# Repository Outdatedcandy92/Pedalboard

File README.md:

# DIY Guitar Pedals

>This project aims to create a DIY friendly and Mod-able version of  the iconic Boss DS-1 and Big Muff Pi.

Modern guitar pedals such as the DS-1 and Big Muff Pi are **super expensive**!! and the new pedals that are being produced all have SMD components which make it harder to mod and repair. I always wanted to get a DS-1 but its price tag really put me off, so I did a bit of research and found a really good circuit analysis of the DS-1 on [ElectroSmash's Website](https://www.electrosmash.com/boss-ds1-analysis) and decided to create my own [DS-1](https://github.com/Outdatedcandy92/DistortionPedal) and it was really rewarding project and the results were also very good. 
Since my DS-1 Version 1 had really good results, I decided to design an even upgraded version of it which fixes problems in version 1, In addition to that I also created a PCB for the Big Muff Pi.

https://github.com/user-attachments/assets/e87293e5-299d-45d1-807d-6a7f5c813e14

https://github.com/user-attachments/assets/bea94fd8-728a-4ede-ab68-e8244417e8f7

*DS-1 PCB*

*Big Muff PCB*

---

### DS-1

### Big Muff Pi

### 3PDT Breakout Board (Optional)

  ---
## BOM

More detailed BOM with parts lists is under the `src` folder 

### DS-1 Components
| **Reference**              | **Value / Part Number**           |
| -------------------------- | --------------------------------- |
| C1, C3                     | 47n                               |
| C2, C8, C9                 | 0.47µF                            |
| C4                         | 250pF                             |
| C5                         | 68n                               |
| C7                         | 100pF                             |
| C10                        | 0.01µF                            |
| C11                        | 0.022µF                           |
| C12                        | 0.1µF                             |
| C13                        | 0.047µF                           |
| C14                        | 1µF                               |
| C15                        | 47µF                              |
| C23                        | 100µF                             |
| D1                         | 1N4004                            |
| D4, D5, D8                 | D1N4148                           |
| Q1, Q2, Q3                 | 2SC2240                           |
| R1, R22                    | 1K                                |
| R2, R7                     | 470K                              |
| R3, R8, R18, R21, R24, R25 | 10K                               |
| R4, R5, R10, R11, R23      | 100K                              |
| R9                         | 22Ω                               |
| R13                        | 4.7K                              |
| R14, R15                   | 2.2K                              |
| R16, R17                   | 6.8K                              |
| R19, R20                   | 1M                                |
| R39                        | 47K                               |
| U1                         | NJM3404A (M5223AL, BA728N equiv.) |
| VR1, VR2                   | 100KB                             |
| VR3                        | 20KB                              |
| J1, J2                     | 6.35mm Jacks                      |
|                            |                                   |

### Big Muff Pi

| **Component Type**       | **Value / Part Number**                           | **Designators**                     |
|--------------------------|---------------------------------------------------|-------------------------------------|
| NPN Transistors          | BC239 or 2N5088, 2N5089, BC549C, SE4010, 2N5210   | Q1, Q2, Q3, Q4                      |
| Silicon Diodes           | 1N914 or 1N4148                                   | D1, D2, D3, D4                      |
| Potentiometers (Lin)     | 100K                                              | Sustain, Tone, Volume              |
| Resistors                | 10K                                               | R13, R19, R18, R11, R12            |
| Resistors                | 100K                                              | R20, R16, R3                       |
| Resistors                | 470K                                              | R9, R17, R15                       |
| Resistors                | 39K                                               | R2, R8                             |
| Resistors                | 150                                               | R21, R10                           |
| Resistors                | 15K                                               | R6                                 |
| Resistor                 | 47K                                               | R14                                |
| Resistor                 | 100                                               | R22                                |
| Resistor                 | 3.3K                                              | R4                                 |
| Resistor                 | 1K                                                | R23                                |
| Resistor                 | 22K                                               | R5                                 |
| Capacitors               | 1µF                                               | C1, C4, C6, C7                     |
| Capacitors               | 100nF                                             | C5, C13, C3, C2                    |
| Capacitors               | 470pF                                             | C10, C11, C12                      |
| Capacitor                | 4nF                                               | C9                                 |
| Capacitor                | 10nF                                              | C8                                 |

#### Credits

[ElectroSmash Boss DS-1 Analysis](https://www.electrosmash.com/boss-ds1-analysis)
[ElectroSmash Big Muff Pi Analysis](https://www.electrosmash.com/big-muff-pi-analysis)

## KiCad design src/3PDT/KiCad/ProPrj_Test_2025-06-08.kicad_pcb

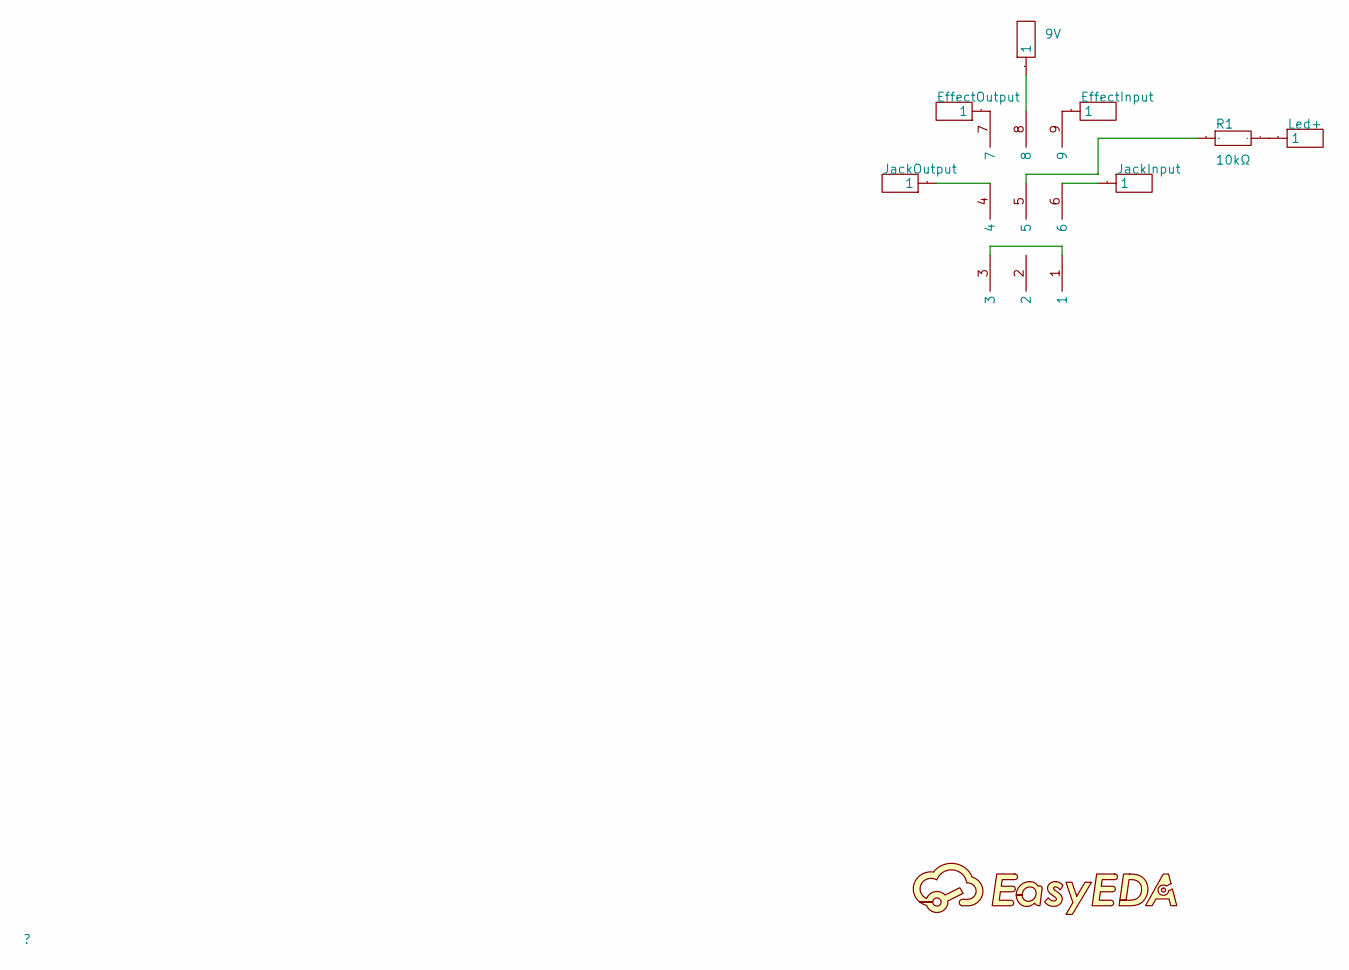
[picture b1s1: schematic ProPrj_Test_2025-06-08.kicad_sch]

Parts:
9V: HDR-TH_1P-V-M_XKB_X4611WV-01I-C28D40
EffectInput: HDR-TH_1P-V-M_XKB_X4611WV-01I-C28D40
EffectOutput: HDR-TH_1P-V-M_XKB_X4611WV-01I-C28D40
JackInput: HDR-TH_1P-V-M_XKB_X4611WV-01I-C28D40
JackOutput: HDR-TH_1P-V-M_XKB_X4611WV-01I-C28D40
Led+: HDR-TH_1P-V-M_XKB_X4611WV-01I-C28D40
R1: 10kΩ; R_AXIAL-0.4
U4: 3dpt

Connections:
$1N369: U4.1, U4.3
$1N418: JackOutput.1, U4.4
$1N421: JackInput.1, U4.6
$1N548: EffectInput.1, U4.9
$1N590: EffectOutput.1, U4.7
$1N612: 9V.1, U4.8
$1N706: Led+.1, R1.2
$1N710: R1.1, U4.5

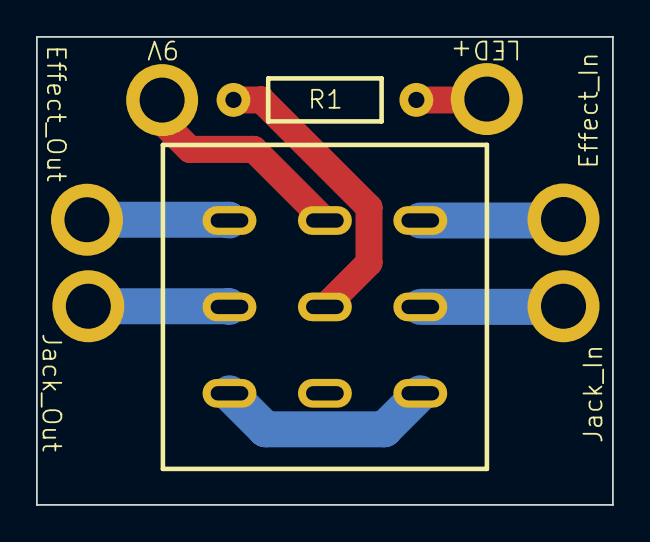
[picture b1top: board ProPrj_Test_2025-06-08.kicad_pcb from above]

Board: 2 copper layers, 32.0 x 26.0 mm, 8 parts (0 on the bottom side), 8 nets.

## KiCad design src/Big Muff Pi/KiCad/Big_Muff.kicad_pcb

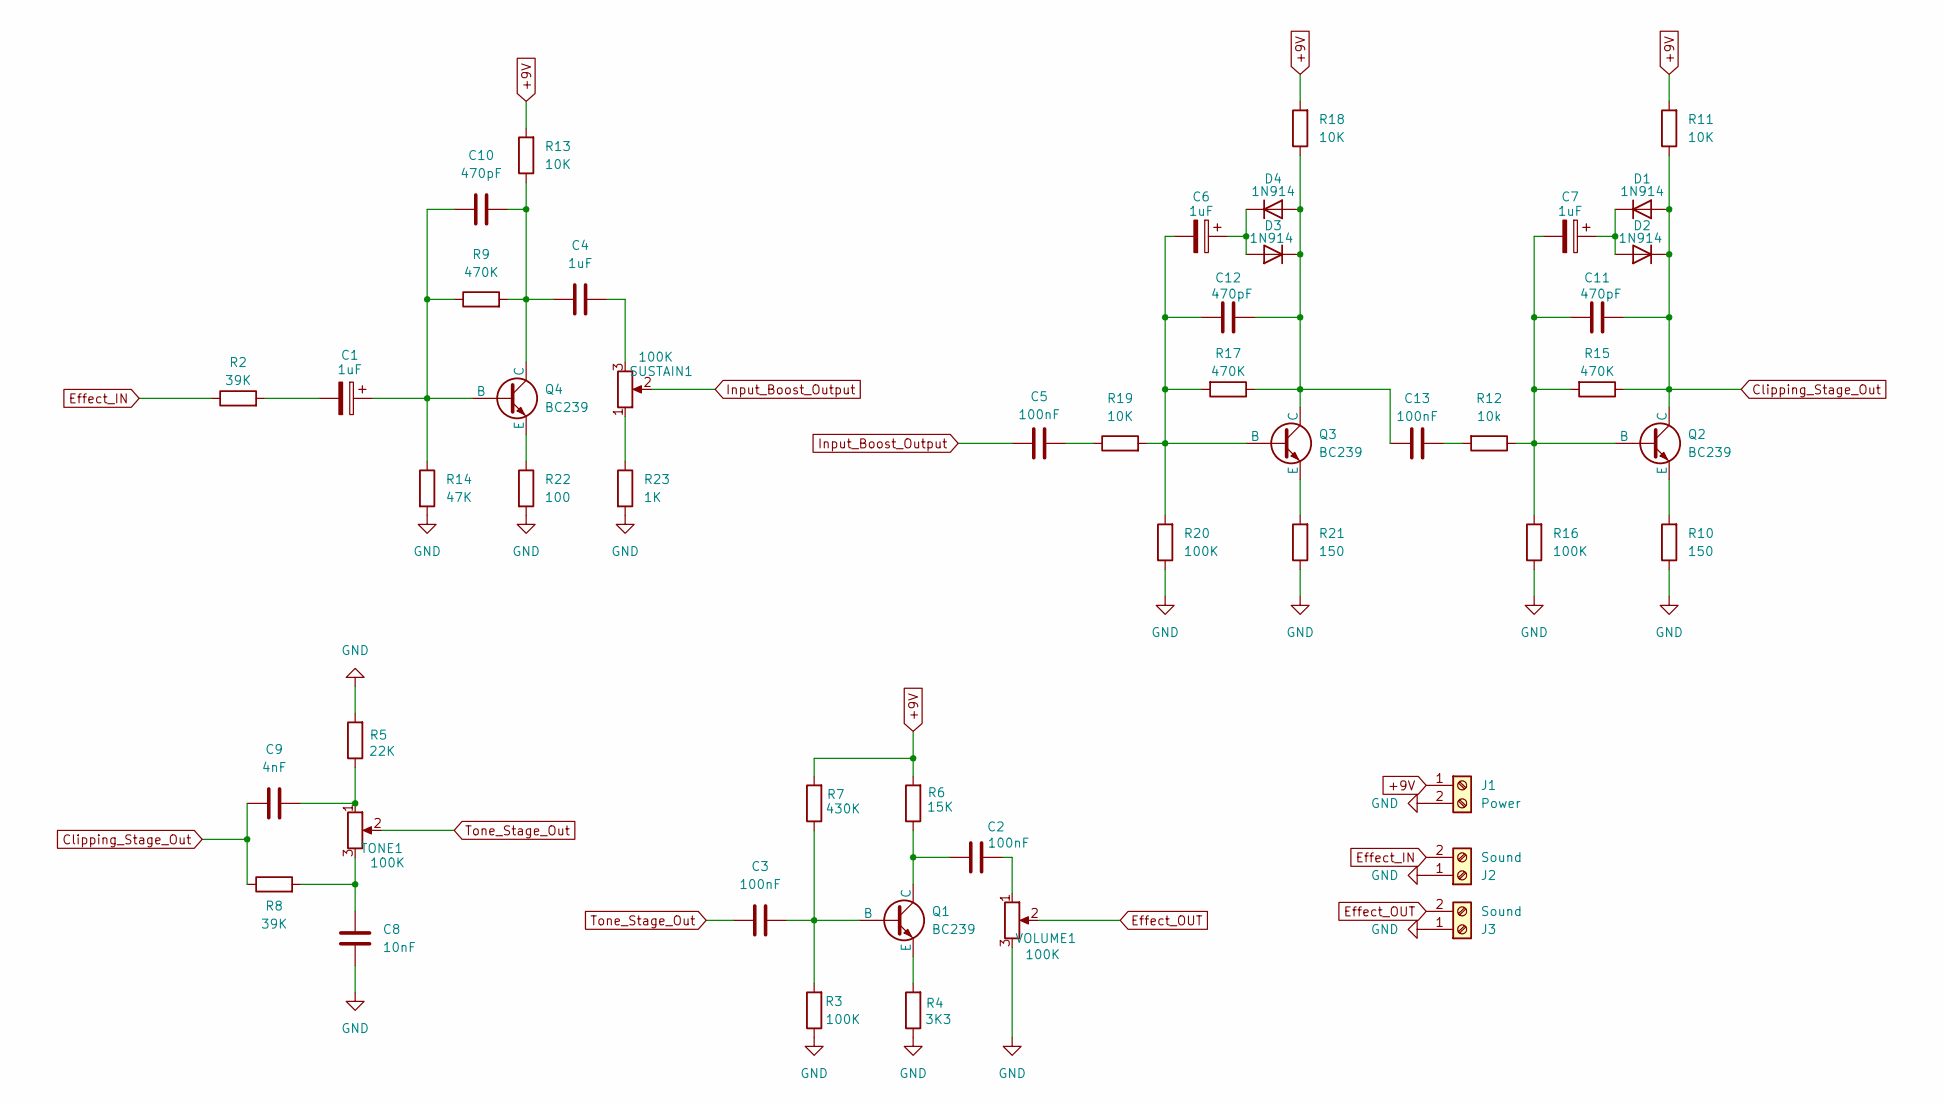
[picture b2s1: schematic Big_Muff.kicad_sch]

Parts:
C1, C6, C7: 1uF; CP_Radial_D5.0mm_P2.50mm
C2, C3, C5, C13: 100nF; C_Disc_D3.0mm_W2.0mm_P2.50mm
C4: 1uF; C_Disc_D3.0mm_W2.0mm_P2.50mm
C8: 10nF; C_Disc_D3.0mm_W2.0mm_P2.50mm
C9: 4nF; C_Disc_D3.0mm_W2.0mm_P2.50mm
C10, C11, C12: 470pF; C_Disc_D3.0mm_W2.0mm_P2.50mm
D1, D2, D3, D4: 1N914; D_DO-35_SOD27_P7.62mm_Horizontal
J1: Power; TerminalBlock_Phoenix_MPT-0,5-2-2.54_1x02_P2.54mm_Horizontal
J2, J3: Sound; TerminalBlock_Phoenix_MPT-0,5-2-2.54_1x02_P2.54mm_Horizontal
Q1, Q2, Q3, Q4: BC239; TO-92_Inline_Wide
R2, R8: 39K; R_Axial_DIN0207_L6.3mm_D2.5mm_P10.16mm_Horizontal
R3, R16, R20: 100K; R_Axial_DIN0207_L6.3mm_D2.5mm_P10.16mm_Horizontal
R4: 3K3; R_Axial_DIN0207_L6.3mm_D2.5mm_P10.16mm_Horizontal
R5: 22K; R_Axial_DIN0207_L6.3mm_D2.5mm_P10.16mm_Horizontal
R6: 15K; R_Axial_DIN0207_L6.3mm_D2.5mm_P10.16mm_Horizontal
R7: 430K; R_Axial_DIN0207_L6.3mm_D2.5mm_P10.16mm_Horizontal
R9, R15, R17: 470K; R_Axial_DIN0207_L6.3mm_D2.5mm_P10.16mm_Horizontal
R10, R21: 150; R_Axial_DIN0207_L6.3mm_D2.5mm_P10.16mm_Horizontal
R11, R13, R18, R19: 10K; R_Axial_DIN0207_L6.3mm_D2.5mm_P10.16mm_Horizontal
R12: 10k; R_Axial_DIN0207_L6.3mm_D2.5mm_P10.16mm_Horizontal
R14: 47K; R_Axial_DIN0207_L6.3mm_D2.5mm_P10.16mm_Horizontal
R22: 100; R_Axial_DIN0207_L6.3mm_D2.5mm_P10.16mm_Horizontal
R23: 1K; R_Axial_DIN0207_L6.3mm_D2.5mm_P10.16mm_Horizontal
SUSTAIN1: 100K; TerminalBlock_Phoenix_MPT-0,5-3-2.54_1x03_P2.54mm_Horizontal
TONE1: 100K; TerminalBlock_Phoenix_MPT-0,5-3-2.54_1x03_P2.54mm_Horizontal
VOLUME1: 100K; TerminalBlock_Phoenix_MPT-0,5-3-2.54_1x03_P2.54mm_Horizontal

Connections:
+9V: J1.1, R6.2, R7.2, R11.2, R13.2, R18.2
Clipping_Stage_Out: C9.1, C11.2, D1.2 (A), D2.1 (K), Q2.1 (C), R8.1, R11.1, R15.1
Effect_IN: J2.2, R2.1
Effect_OUT: J3.2, VOLUME1.2; also elsewhere on the board
GND: C8.1, J1.2, J2.1, J3.1, R3.1, R4.1, R5.2, R10.1, R14.2, R16.1, R20.1, R21.1, R22.2, R23.2, VOLUME1.3; also elsewhere on the board
Input_Boost_Output: C5.1, SUSTAIN1.2; also elsewhere on the board
unnamed: C1.2, R2.2
unnamed 7: C2.2, VOLUME1.1; also elsewhere on the board
unnamed 8: C4.2, SUSTAIN1.3; also elsewhere on the board
unnamed: C5.2, R19.1
unnamed 10: C8.2, R8.2, TONE1.3; also elsewhere on the board
unnamed 11: C9.2, R5.1, TONE1.1; also elsewhere on the board
unnamed: C13.2, R12.2
unnamed: C7.1, D1.1 (K), D2.2 (A)
unnamed: C6.1, D3.2 (A), D4.1 (K)
unnamed: C12.2, C13.1, D3.1 (K), D4.2 (A), Q3.1 (C), R17.1, R18.1
unnamed: C3.2, Q1.2 (B), R3.2, R7.1
unnamed: C2.1, Q1.1 (C), R6.1
unnamed: Q1.3 (E), R4.2
unnamed: C7.2, C11.1, Q2.2 (B), R12.1, R15.2, R16.2
unnamed: Q2.3 (E), R10.2
unnamed: C6.2, C12.1, Q3.2 (B), R17.2, R19.2, R20.2
unnamed: Q3.3 (E), R21.2
unnamed: C1.1, C10.1, Q4.2 (B), R9.1, R14.1
unnamed: C4.1, C10.2, Q4.1 (C), R9.2, R13.1
unnamed: Q4.3 (E), R22.1
unnamed 26: R23.1, SUSTAIN1.1; also elsewhere on the board
Tone_Stage_Out: C3.1, TONE1.2; also elsewhere on the board

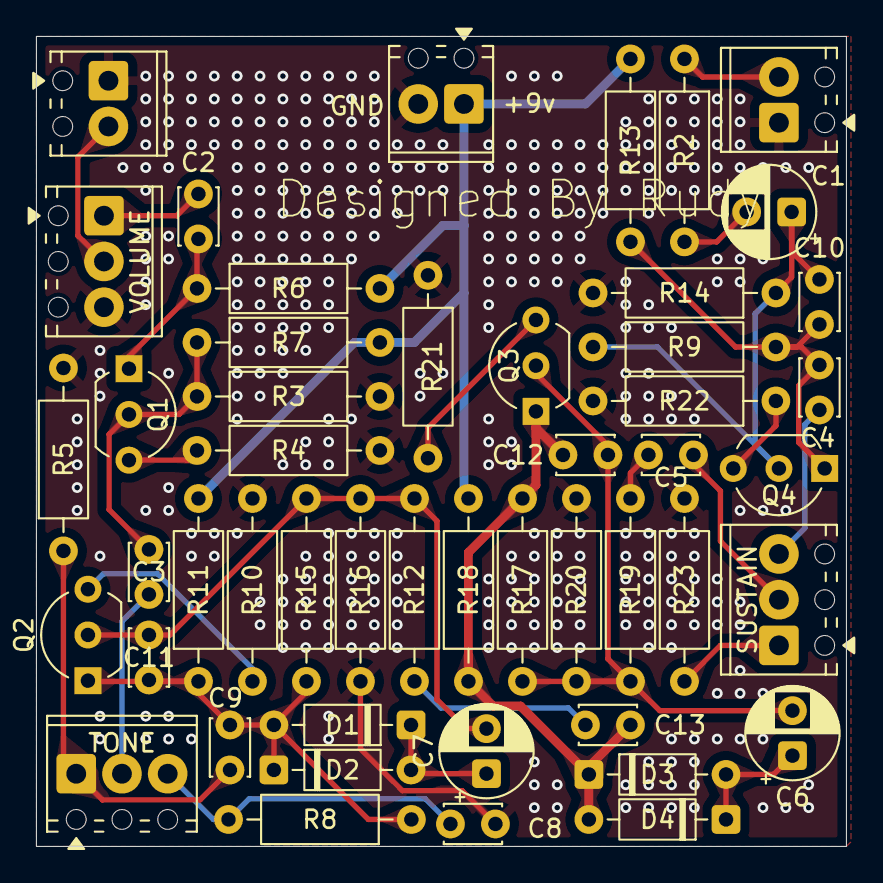
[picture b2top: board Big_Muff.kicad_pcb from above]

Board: 2 copper layers, 45.0 x 45.0 mm, 49 parts (0 on the bottom side), 28 nets.

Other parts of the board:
SUSTAIN: 100K; TerminalBlock_Phoenix_MPT-0,5-3-2.54_1x03_P2.54mm_Horizontal
TONE: 100K; TerminalBlock_Phoenix_MPT-0,5-3-2.54_1x03_P2.54mm_Horizontal
VOLUME: 100K; TerminalBlock_Phoenix_MPT-0,5-3-2.54_1x03_P2.54mm_Horizontal

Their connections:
Effect_OUT: VOLUME.2; also elsewhere on the board
GND: VOLUME.3; also elsewhere on the board
Input_Boost_Output: SUSTAIN.2; also elsewhere on the board
unnamed 7: VOLUME.1; also elsewhere on the board
unnamed 8: SUSTAIN.3; also elsewhere on the board
unnamed 10: TONE.3; also elsewhere on the board
unnamed 11: TONE.1; also elsewhere on the board
unnamed 26: SUSTAIN.1; also elsewhere on the board
Tone_Stage_Out: TONE.2; also elsewhere on the board

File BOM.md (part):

| **Component Type**          | **Value / Part Number**                                                                      | **Quantity** | Link                                                                                                                                                                                                                                                                                                                                                                                                                                                                                                                                                                                                               | Price                |
| --------------------------- | -------------------------------------------------------------------------------------------- | ------------ | ------------------------------------------------------------------------------------------------------------------------------------------------------------------------------------------------------------------------------------------------------------------------------------------------------------------------------------------------------------------------------------------------------------------------------------------------------------------------------------------------------------------------------------------------------------------------------------------------------------------ | -------------------- |
| **Transistor**              | 2SC2240                                                                                      | 3            | [100pcs 2SC2240](https://www.aliexpress.com/item/1005009095677131.html?spm=a2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                                                                                                              | $3.33                |
|                             | BC239 or equiv. (2N5088, etc.)                                                               | 4            | [50pcs BC239B](https://www.aliexpress.com/item/1005005902190106.html?spm=a2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                                                                                                                 | $3.02                |
| **Diode**                   | 1N4004                                                                                       | 1            | [50pcs 1N4004](https://www.aliexpress.com/item/1005008196083877.html?spm=a2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                                                                                                               | $1.96                |
|                             | 1N4148 / 1N914                                                                               | 7            | [100pcs 1N4148](https://www.aliexpress.com/item/4000142272546.html?spm=a2g0o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                                                                                                             | $2.81                |
| **IC**                      | NJM3404A / M5223AL / BA728N <br>*Note: these chips are hard to find so I'm using a NJM4558L* | 1            | [10pcs NJM4558L](https://www.aliexpress.com/item/33046960877.html?spm=a2g0o.p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                                                                                                                         | $3.03                |
| **Potentiometer**           | 100KB                                                                                        | 5            | [10pcs WH148](https://www.aliexpress.com/item/1005004591016818.html?spm=a2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 | $3.82                |
|                             | 20KB                                                                                         | 1            | [10pcs WH148](https://www.aliexpress.com/item/1005004591016818.html?spm=a2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 | $3.83                |
| **Connector**               | 6.35mm Jack                                                                                  | 4            | [10pcs Mono TS Jack](https://www.aliexpress.com/item/1005006997184592.html?spm=a2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      | $5.99                |
|                             | Screw In Terminal (2 Pin)                                                                    | 4            | [10pcs 2 Pin Terminal](https://www.aliexpress.com/item/1005001677869988.html?spm=a2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                                                                                                      | $2.73                |
|                             | Screw In Terminal (3 Pin)                                                                    | 6            | [10pcs 3 Pin Terminal](https://www.aliexpress.com/item/1005001677869988.html?spm=a2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                                                                                                      | $3.04                |
| **Resistor**                | 22Ω                                                                                          | 1            | [600pcs Resistor Set](https://www.aliexpress.com/item/1005005855324735.html?spm=a2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                                                                                                       | $4.79                |
|                             | 100Ω                                                                                         | 1            |                                                                                                                                                                                                                                                                                                                                                                                                                                                                                                                                                                                                                    |                      |
|                             | 150Ω                                                                                         | 2            |                                                                                                                                                                                                                                                                                                                                                                                                                                                                                                                                                                                                                    |                      |
|                             | 1K                                                                                           | 3            |                                                                                                                                                                                                                                                                                                                                                                                                                                                                                                                                                                                                                    |                      |
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
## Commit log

2025-07-29 journal update
